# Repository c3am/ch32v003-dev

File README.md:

# ch32v003-dev
This is a minimal ch32v003 devboard developed in kicad.

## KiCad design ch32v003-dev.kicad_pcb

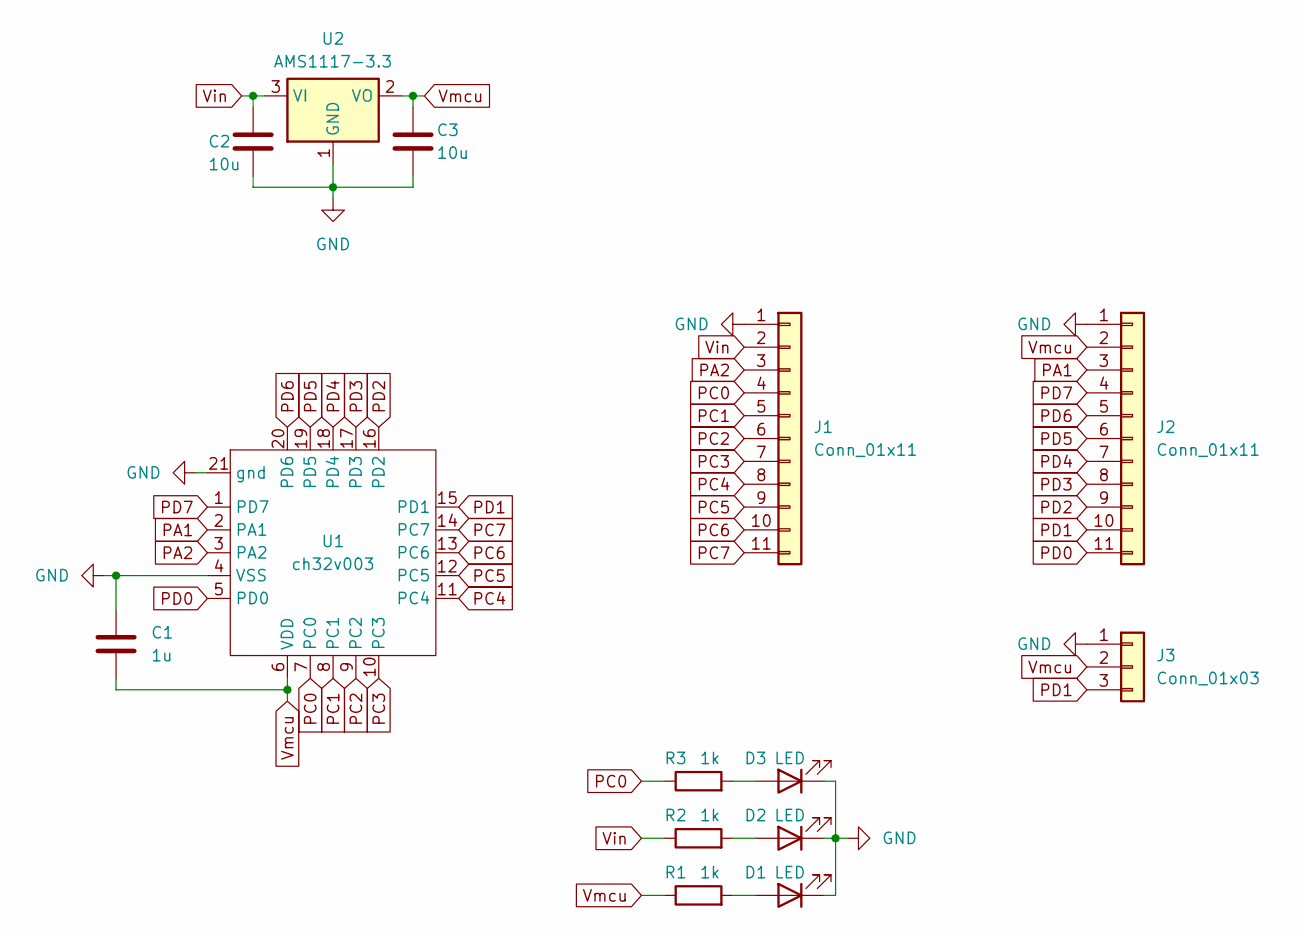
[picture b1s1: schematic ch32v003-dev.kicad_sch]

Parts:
C1: 1u; C_0603_1608Metric
C2, C3: 10u; C_0603_1608Metric
D1, D2, D3: LED; LED-0603-1608
J1, J2: Conn_01x11; pin-header-2.5mm-11
J3: Conn_01x03; pin-header-2.5mm-3
R1, R2, R3: 1k; R_0603_1608Metric
U1: ch32v003; QFN-20-1EP_3x3mm_P0.4mm_EP1.65x1.65mm
U2: AMS1117-3.3; SOT-23-3

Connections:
GND: C1.1, C2.2, C3.2, D1.1 (K), D2.1 (K), D3.1 (K), J1.1, J2.1, J3.1, U1.4 (VSS), U1.21 (gnd), U2.1 (GND)
unnamed: D1.2 (A), R1.2
unnamed: D2.2 (A), R2.2
unnamed: D3.2 (A), R3.2
PA1: J2.3, U1.2 (PA1)
PA2: J1.3, U1.3 (PA2)
PC0: J1.4, R3.1, U1.7 (PC0)
PC1: J1.5, U1.8 (PC1)
PC2: J1.6, U1.9 (PC2)
PC3: J1.7, U1.10 (PC3)
PC4: J1.8, U1.11 (PC4)
PC5: J1.9, U1.12 (PC5)
PC6: J1.10, U1.13 (PC6)
PC7: J1.11, U1.14 (PC7)
PD0: J2.11, U1.5 (PD0)
PD1: J2.10, J3.3, U1.15 (PD1)
PD2: J2.9, U1.16 (PD2)
PD3: J2.8, U1.17 (PD3)
PD4: J2.7, U1.18 (PD4)
PD5: J2.6, U1.19 (PD5)
PD6: J2.5, U1.20 (PD6)
PD7: J2.4, U1.1 (PD7)
Vin: C2.1, J1.2, R2.1, U2.3 (VI)
Vmcu: C1.2, C3.1, J2.2, J3.2, R1.1, U1.6 (VDD), U2.2 (VO)

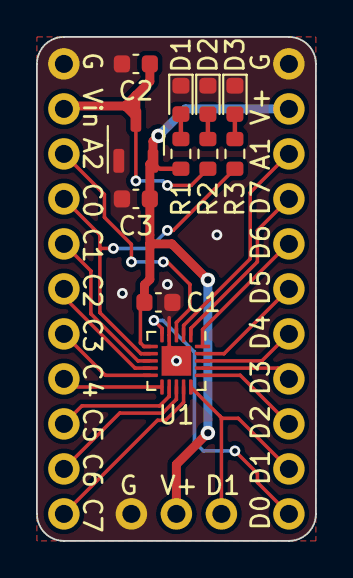
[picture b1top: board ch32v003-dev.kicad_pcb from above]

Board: 2 copper layers, 15.5 x 28.0 mm, 14 parts (1 on the bottom side), 24 nets.

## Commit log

2023-12-02 project file upload
2025-04-19 added images
2025-04-19 updated readme again
2025-04-19 rotated images
